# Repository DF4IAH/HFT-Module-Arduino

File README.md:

# HFT-Module-Arduino
Arduino compatible module to be attached at the HFT-Core-Module developed by the HFT Institute @ HS-MA

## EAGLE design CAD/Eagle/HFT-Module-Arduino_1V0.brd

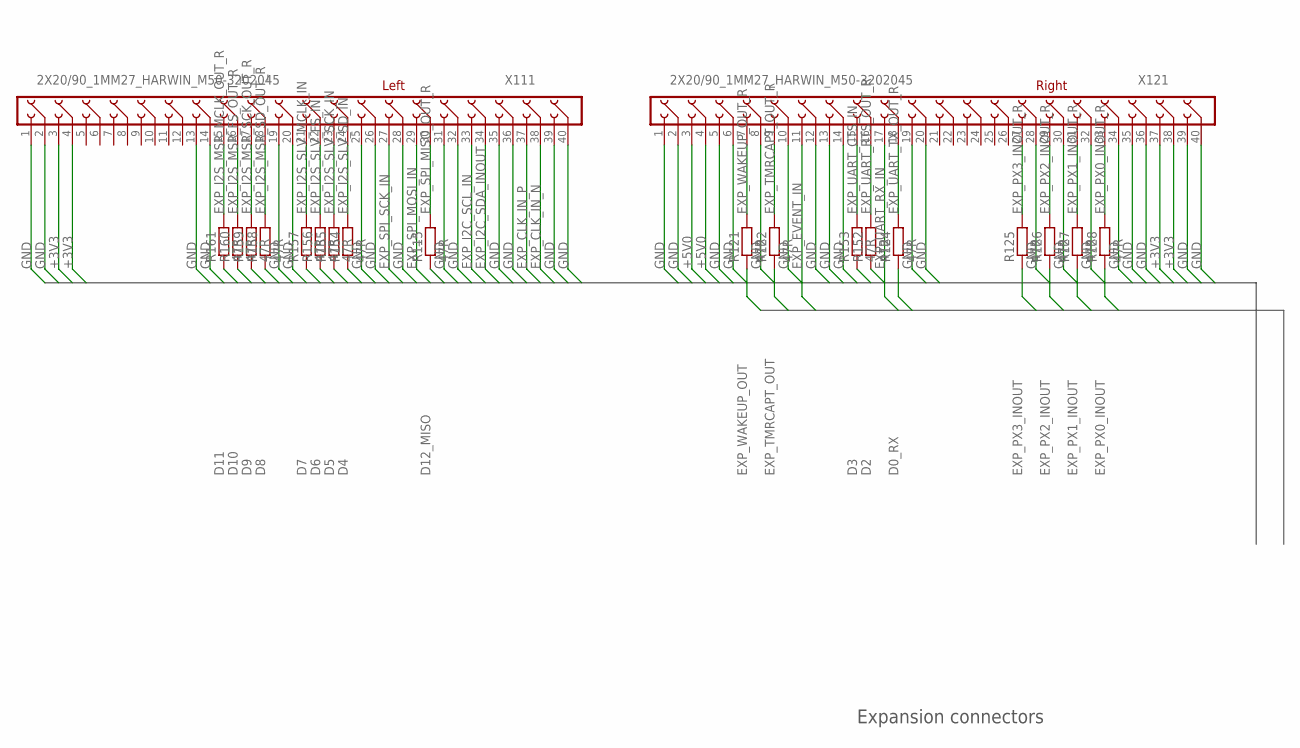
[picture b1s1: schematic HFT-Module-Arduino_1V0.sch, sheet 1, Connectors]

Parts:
R115, R121, R122, R124, R125, R126, R127, R128, R152, R153, R154, R155, R156, R157, R158, R159, R160, R161: 47R; R0805
X111, X121: 2X20/90_1MM27_HARWIN_M50-3202045

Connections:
+3V3: X111.3, X111.4, X121.37, X121.38; also elsewhere on the board
+5V0: X121.3, X121.4; also elsewhere on the board
D0_RX: R124.1; also elsewhere on the board
D2: R152.1; also elsewhere on the board
D3: R153.1; also elsewhere on the board
D4: R154.1; also elsewhere on the board
D5: R155.1; also elsewhere on the board
D6: R156.1; also elsewhere on the board
D7: R157.1; also elsewhere on the board
D8: R158.1; also elsewhere on the board
D9: R159.1; also elsewhere on the board
D10: R160.1; also elsewhere on the board
D11: R161.1; also elsewhere on the board
D12_MISO: R115.1; also elsewhere on the board
EXP_CLK_IN_N: X111.38
EXP_CLK_IN_P: X111.37
EXP_EVENT_IN: X121.11; also elsewhere on the board
EXP_I2C_SCL_IN: X111.33; also elsewhere on the board
EXP_I2C_SDA_INOUT: X111.34; also elsewhere on the board
EXP_I2S_MSR_FS_OUT_R: R160.2, X111.16
EXP_I2S_MSR_MCLK_OUT_R: R161.2, X111.15
EXP_I2S_MSR_SCK_OUT_R: R159.2, X111.17
EXP_I2S_MSR_SD_OUT_R: R158.2, X111.18
EXP_I2S_SLV_FS_IN: R156.2, X111.22
EXP_I2S_SLV_MCLK_IN: R157.2, X111.21
EXP_I2S_SLV_SCK_IN: R155.2, X111.23
EXP_I2S_SLV_SD_IN: R154.2, X111.24
EXP_PX0_INOUT: R128.1; also elsewhere on the board
EXP_PX0_INOUT_R: R128.2, X121.33
EXP_PX1_INOUT: R127.1; also elsewhere on the board
EXP_PX1_INOUT_R: R127.2, X121.31
EXP_PX2_INOUT: R126.1; also elsewhere on the board
EXP_PX2_INOUT_R: R126.2, X121.29
EXP_PX3_INOUT: R125.1; also elsewhere on the board
EXP_PX3_INOUT_R: R125.2, X121.27
EXP_SPI_MISO_OUT_R: R115.2, X111.30
EXP_SPI_MOSI_IN: X111.29; also elsewhere on the board
EXP_SPI_SCK_IN: X111.27; also elsewhere on the board
EXP_TMRCAPT_OUT: R122.1; also elsewhere on the board
EXP_TMRCAPT_OUT_R: R122.2, X121.9
EXP_UART_CTS_IN: R153.2, X121.15
EXP_UART_RTS_OUT_R: R152.2, X121.16
EXP_UART_RX_IN: X121.17; also elsewhere on the board
EXP_UART_TX_OUT_R: R124.2, X121.18
EXP_WAKEUP_OUT: R121.1; also elsewhere on the board
EXP_WAKEUP_OUT_R: R121.2, X121.7
GND: X111.1, X111.2, X111.13, X111.14, X111.19, X111.20, X111.25, X111.26, X111.28, X111.31, X111.32, X111.35, X111.36, X111.39, X111.40, X121.1, X121.2, X121.5, X121.6, X121.8, X121.10, X121.12, X121.13, X121.14, X121.19, X121.20, X121.28, X121.30, X121.32, X121.34, X121.35, X121.36, X121.39, X121.40; also elsewhere on the board

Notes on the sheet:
Left
Right
Expansion connectors

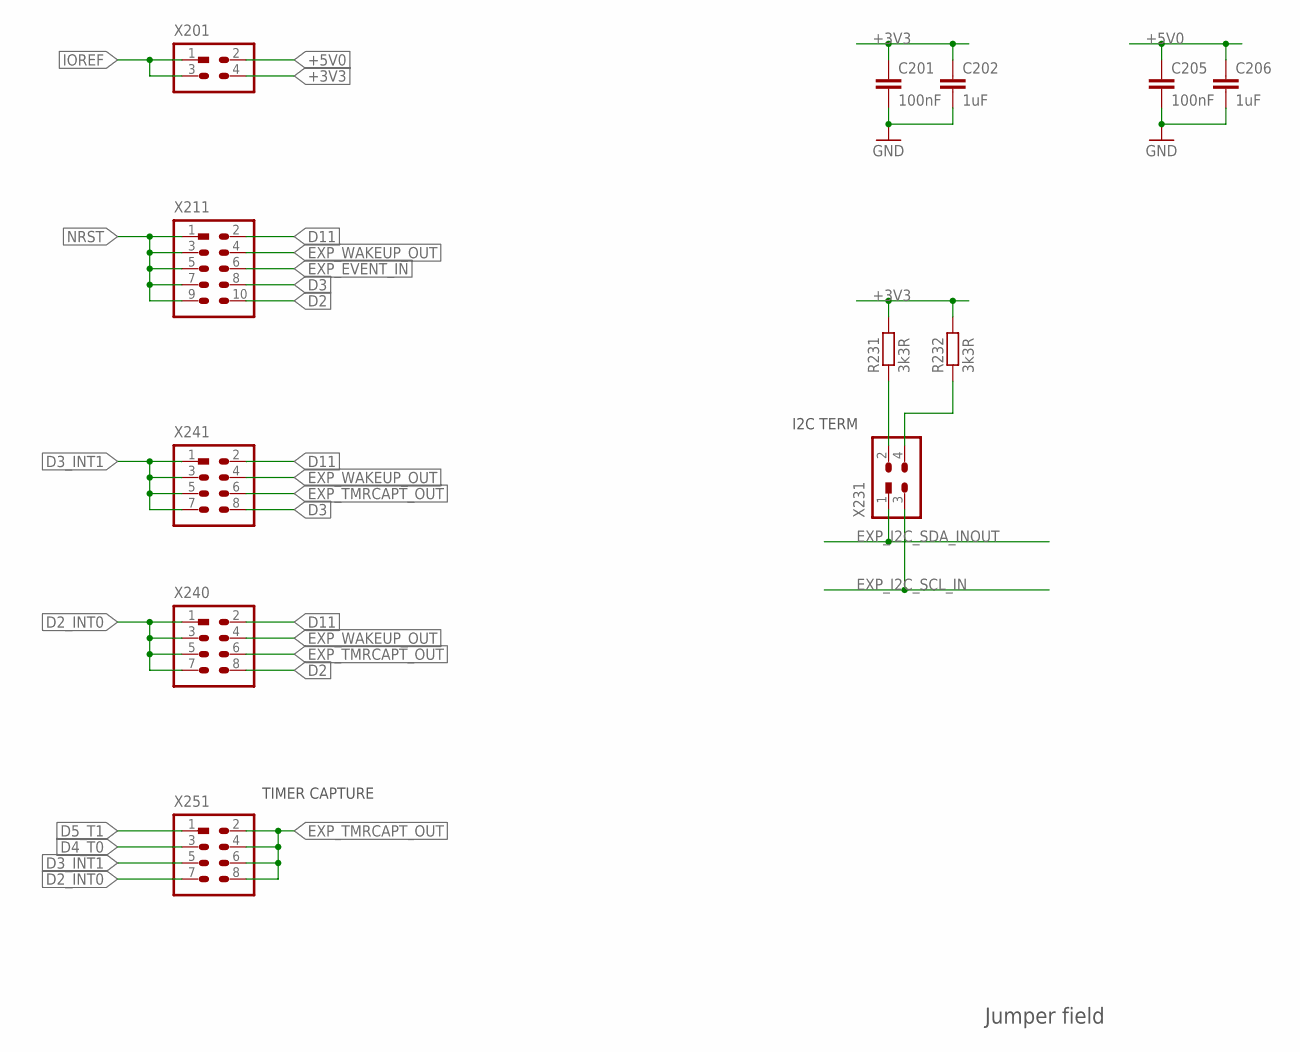
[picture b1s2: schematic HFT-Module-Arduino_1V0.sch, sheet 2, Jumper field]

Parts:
C201, C205: 100nF; C0805
C202, C206: 1uF; C0805
R231, R232: 3k3R; R0805
X201, X231: HEADER-2X2; 2X02
X211: HEADER-2X5; 2X05
X240, X241, X251: HEADER-2X4; 2X04

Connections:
+3V3: C201.1, C202.1, R231.2, R232.2, X201.4; also elsewhere on the board
+5V0: C205.1, C206.1, X201.2; also elsewhere on the board
D2: X211.10, X240.8; also elsewhere on the board
D2_INT0: X240.1, X240.3, X240.5, X240.7, X251.7; also elsewhere on the board
D3: X211.8, X241.8; also elsewhere on the board
D3_INT1: X241.1, X241.3, X241.5, X241.7, X251.5; also elsewhere on the board
D4_T0: X251.3; also elsewhere on the board
D5_T1: X251.1; also elsewhere on the board
D11: X211.2, X240.2, X241.2; also elsewhere on the board
EXP_EVENT_IN: X211.6; also elsewhere on the board
EXP_I2C_SCL_IN: X231.3; also elsewhere on the board
EXP_I2C_SDA_INOUT: X231.1; also elsewhere on the board
EXP_TMRCAPT_OUT: X240.6, X241.6, X251.2, X251.4, X251.6, X251.8; also elsewhere on the board
EXP_WAKEUP_OUT: X211.4, X240.4, X241.4; also elsewhere on the board
GND: C201.2, C202.2, C205.2, C206.2; also elsewhere on the board
IOREF: X201.1, X201.3; also elsewhere on the board
NRST: X211.1, X211.3, X211.5, X211.7, X211.9; also elsewhere on the board
SCL_TERM: R232.1, X231.4
SDA_TERM: R231.1, X231.2

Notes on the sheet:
Jumper field
I2C TERM
TIMER CAPTURE

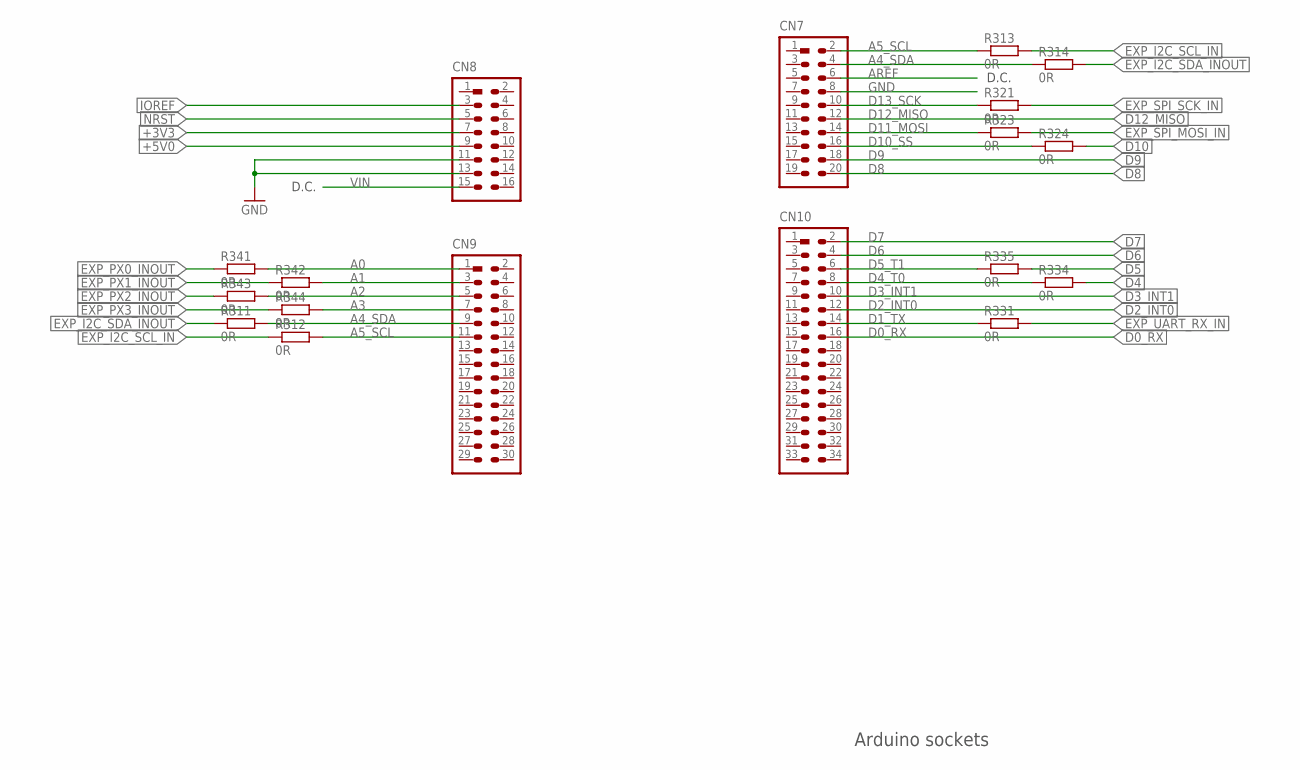
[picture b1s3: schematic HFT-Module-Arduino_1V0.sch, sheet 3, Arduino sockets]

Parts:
CN7: HEADER-2X10; 2X10
CN8: HEADER-2X8; 2X08
CN9: HEADER-2X15; 2X15
CN10: HEADER-2X17; 2X17
R311, R312, R313, R314, R321, R323, R324, R331, R334, R335, R341, R342, R343, R344: 0R; R0805

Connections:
+3V3: CN8.7; also elsewhere on the board
+5V0: CN8.9; also elsewhere on the board
A0: CN9.1, R341.2
A1: CN9.3, R342.2
A2: CN9.5, R343.2
A3: CN9.7, R344.2
A4_SDA: CN7.4, CN9.9, R311.2, R314.1
A5_SCL: CN7.2, CN9.11, R312.2, R313.1
AREF: CN7.6
D0_RX: CN10.16; also elsewhere on the board
D1_TX: CN10.14, R331.1
D2_INT0: CN10.12; also elsewhere on the board
D3_INT1: CN10.10; also elsewhere on the board
D4: R334.2; also elsewhere on the board
D4_T0: CN10.8, R334.1; also elsewhere on the board
D5: R335.2; also elsewhere on the board
D5_T1: CN10.6, R335.1; also elsewhere on the board
D6: CN10.4; also elsewhere on the board
D7: CN10.2; also elsewhere on the board
D8: CN7.20; also elsewhere on the board
D9: CN7.18; also elsewhere on the board
D10: R324.2; also elsewhere on the board
D10_SS: CN7.16, R324.1
D11_MOSI: CN7.14, R323.1
D12_MISO: CN7.12; also elsewhere on the board
D13_SCK: CN7.10, R321.1
EXP_I2C_SCL_IN: R312.1, R313.2; also elsewhere on the board
EXP_I2C_SDA_INOUT: R311.1, R314.2; also elsewhere on the board
EXP_PX0_INOUT: R341.1; also elsewhere on the board
EXP_PX1_INOUT: R342.1; also elsewhere on the board
EXP_PX2_INOUT: R343.1; also elsewhere on the board
EXP_PX3_INOUT: R344.1; also elsewhere on the board
EXP_SPI_MOSI_IN: R323.2; also elsewhere on the board
EXP_SPI_SCK_IN: R321.2; also elsewhere on the board
EXP_UART_RX_IN: R331.2; also elsewhere on the board
GND: CN7.8, CN8.11, CN8.13; also elsewhere on the board
IOREF: CN8.3; also elsewhere on the board
NRST: CN8.5; also elsewhere on the board
VIN: CN8.15

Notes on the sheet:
Arduino sockets
D.C.

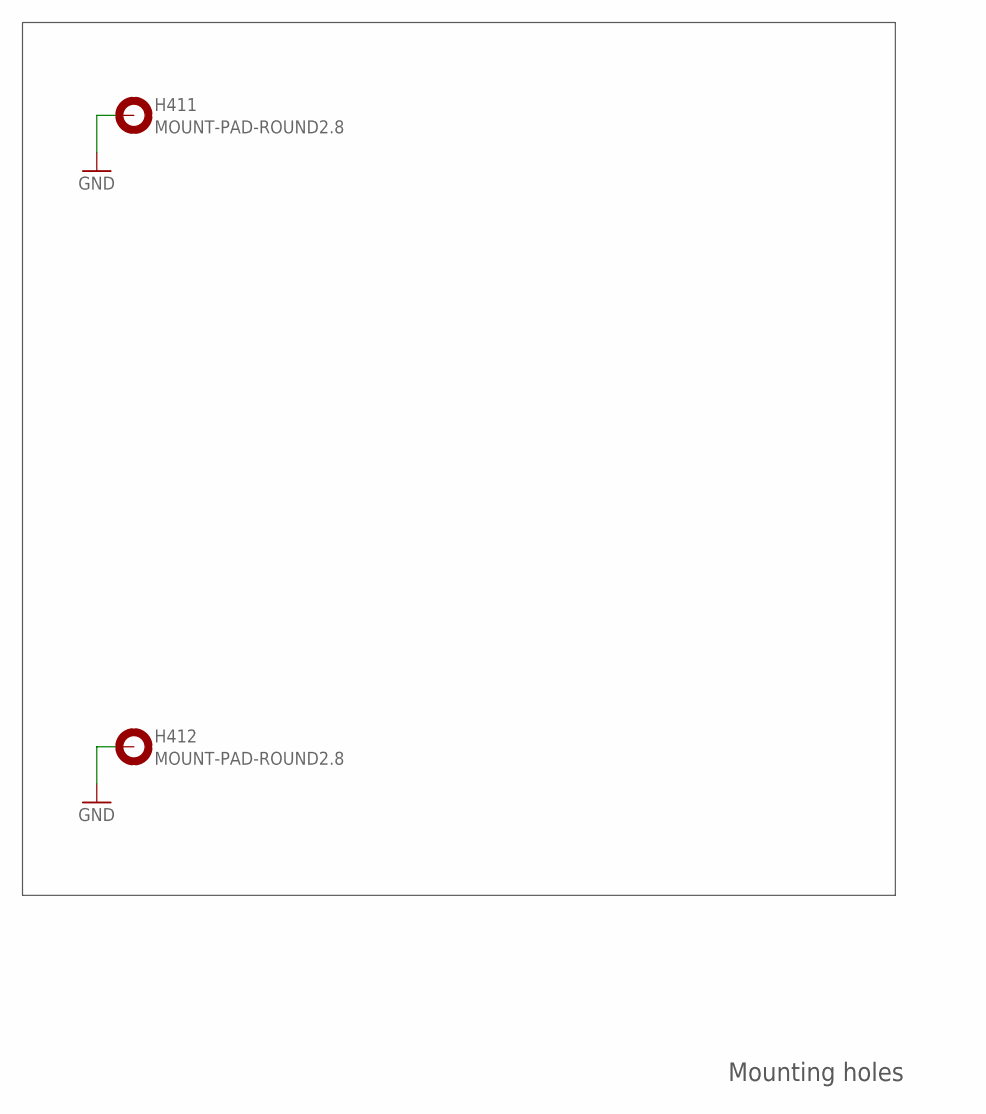
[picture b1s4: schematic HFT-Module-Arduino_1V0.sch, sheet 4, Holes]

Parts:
H411, H412: MOUNT-PAD-ROUND2.8; 2,8-PAD

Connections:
GND: H411.B2,8, H412.B2,8; also elsewhere on the board

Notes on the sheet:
Mounting holes

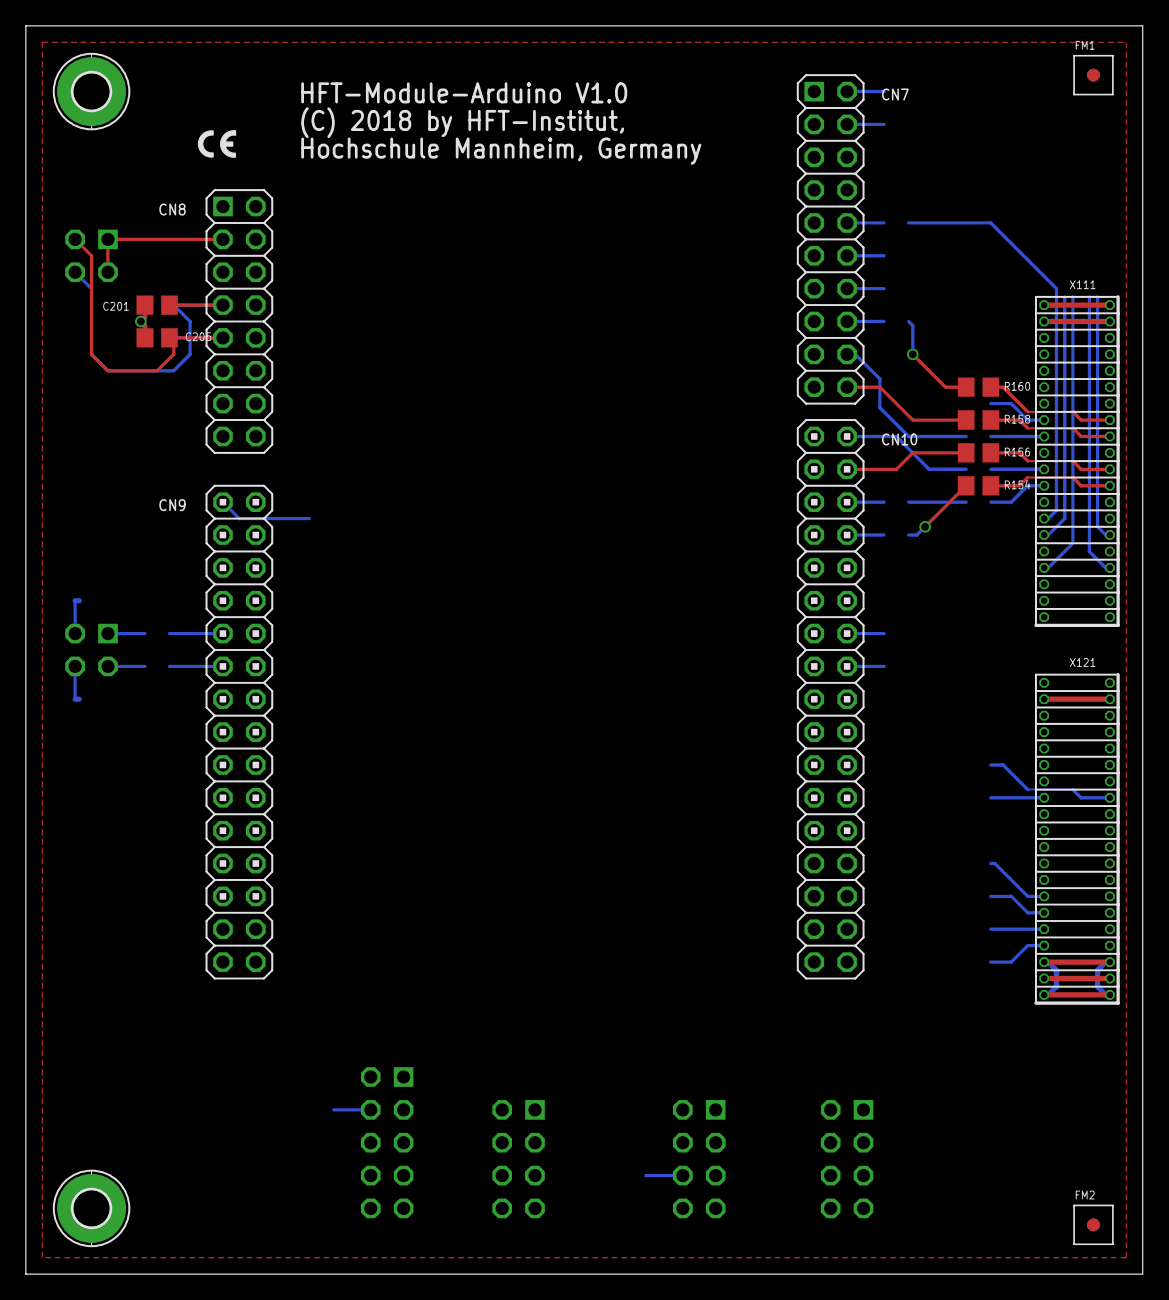
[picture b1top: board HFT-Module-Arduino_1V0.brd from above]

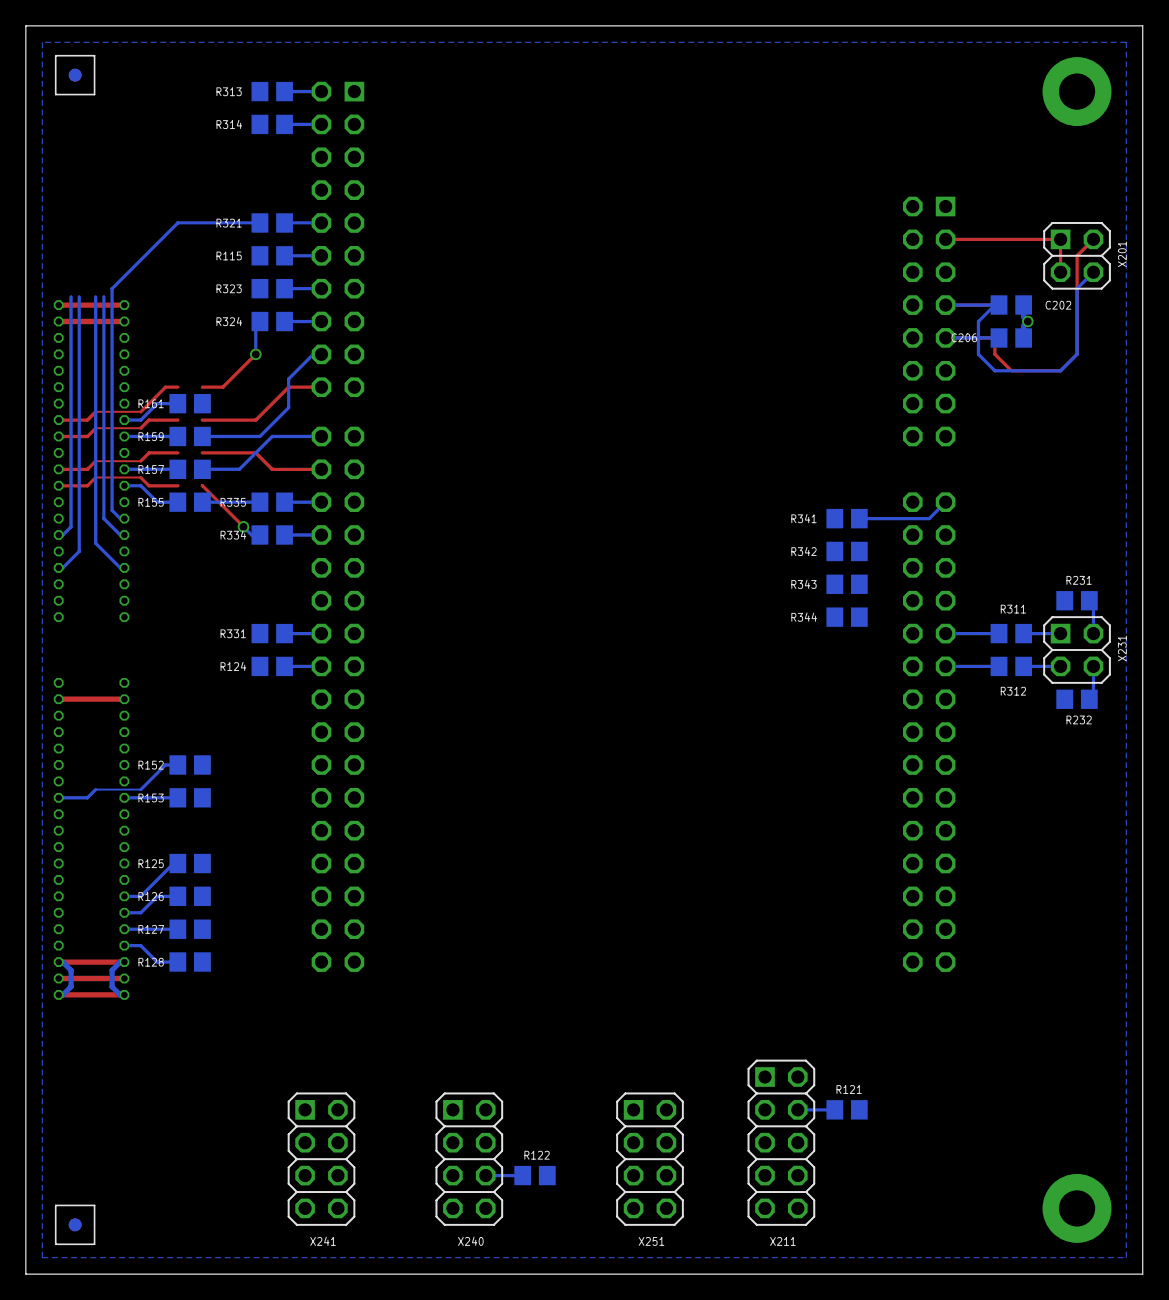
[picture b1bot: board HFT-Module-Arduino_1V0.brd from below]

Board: 4 copper layers, 86.4 x 96.5 mm, 54 parts (38 on the bottom side), 63 nets.

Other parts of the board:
FM1, FM2: FIDUCIAL_MARK_1MM

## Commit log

2018-08-06 Initial set-up and deviation of HFT-Core-Modules
2018-08-06 .gitignore added
2018-08-06 HW_1V0 - Initial setup of PCB
2018-08-07 HW_1V0 - CAD/Eagle - df4iah_connector.lbr - more headers added
2018-08-07 HW_1V0 - CAD/Eagle - Arduino compatible headers added
2018-08-08 HW_1V0 - CAD/Eagle - components placed first round
2018-08-08 DOCS - missing directory added
2018-08-08 HW_1V0 - CAD/Eagle - df4iah_connector.lbr - HEADER-2X4 added
2018-08-08 HW_1V0 - CAD/Eagle - placing finished, routing started

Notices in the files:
CAD/Eagle/HFT-Module-Arduino_1V0.brd:
(C) 2018 by HFT-Institut,
Hochschule Mannheim, Germany
